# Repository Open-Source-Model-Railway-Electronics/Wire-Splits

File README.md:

# Wire-Splits

TODO:
Make sure they can be made with with SMD assembly

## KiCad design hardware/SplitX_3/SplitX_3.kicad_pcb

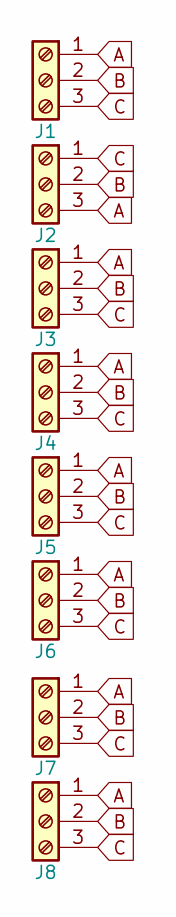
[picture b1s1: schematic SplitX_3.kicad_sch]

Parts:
J1, J2, J3, J4, J5, J6, J7, J8: Screw_Terminal_01x03; TerminalBlock_Phoenix_MKDS-1,5-3-5.08_1x03_P5.08mm_Horizont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

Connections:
A: J1.1, J2.3, J3.1, J4.1, J5.1, J6.1, J7.1, J8.1
B: J1.2, J2.2, J3.2, J4.2, J5.2, J6.2, J7.2, J8.2
C: J1.3, J2.1, J3.3, J4.3, J5.3, J6.3, J7.3, J8.3

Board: 4 copper layers, 8 parts (0 on the bottom side), 3 nets, no tracks yet.

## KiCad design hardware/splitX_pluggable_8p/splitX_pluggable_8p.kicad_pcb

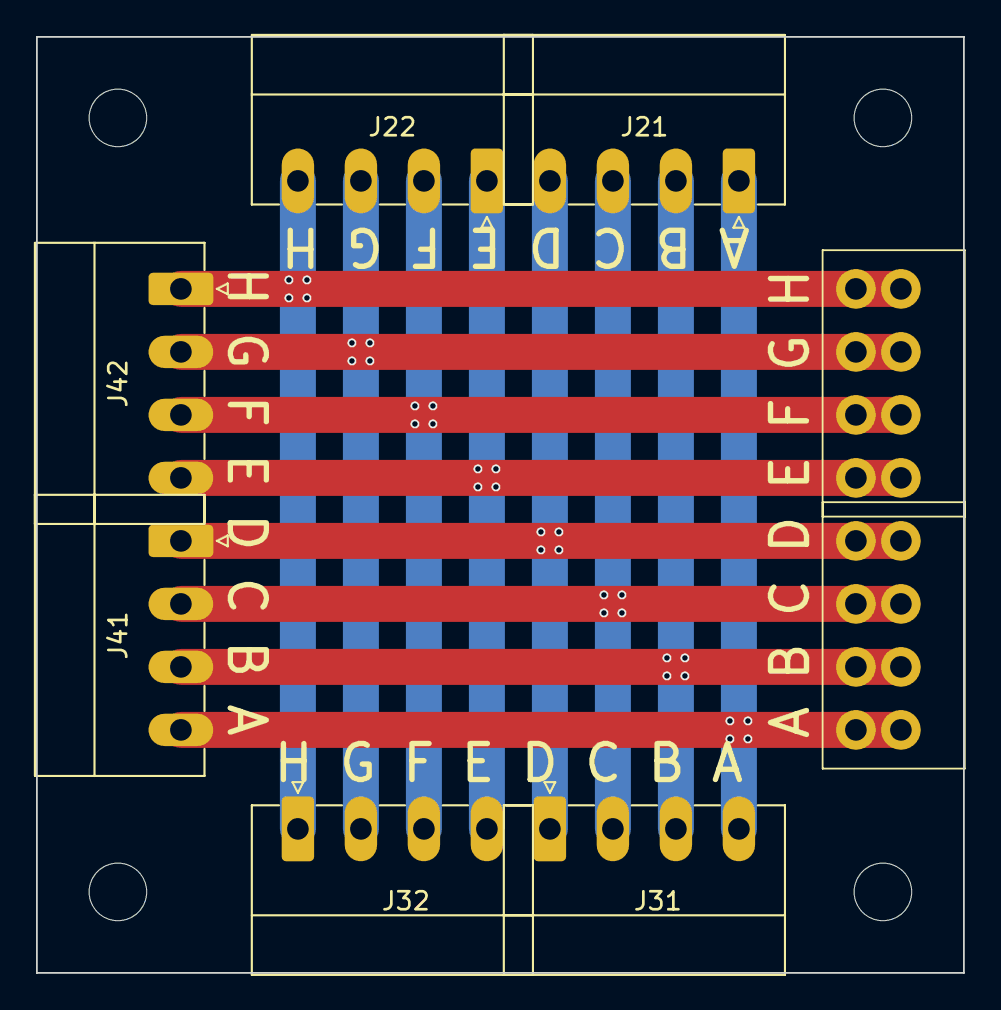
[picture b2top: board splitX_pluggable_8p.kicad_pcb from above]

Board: 2 copper layers, 51.5 x 52.0 mm, 8 parts (0 on the bottom side), 8 nets.

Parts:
J11, J12: MALE; connector_3.50mm_4P horizontal_MALE
J21, J22, J31, J32, J41, J42: FEMALE; PhoenixContact_MC_1,5_4-G-3.5_1x04_P3.50mm_Horizontal

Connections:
unnamed: J11.1, J21.1, J31.4, J41.4
unnamed: J11.2, J21.2, J31.3, J41.3
unnamed: J11.3, J21.3, J31.2, J41.2
unnamed: J11.4, J21.4, J31.1, J41.1
unnamed: J12.1, J22.1, J32.4, J42.4
unnamed: J12.2, J22.2, J32.3, J42.3
unnamed: J12.3, J22.3, J32.2, J42.2
unnamed: J12.4, J22.4, J32.1, J42.1

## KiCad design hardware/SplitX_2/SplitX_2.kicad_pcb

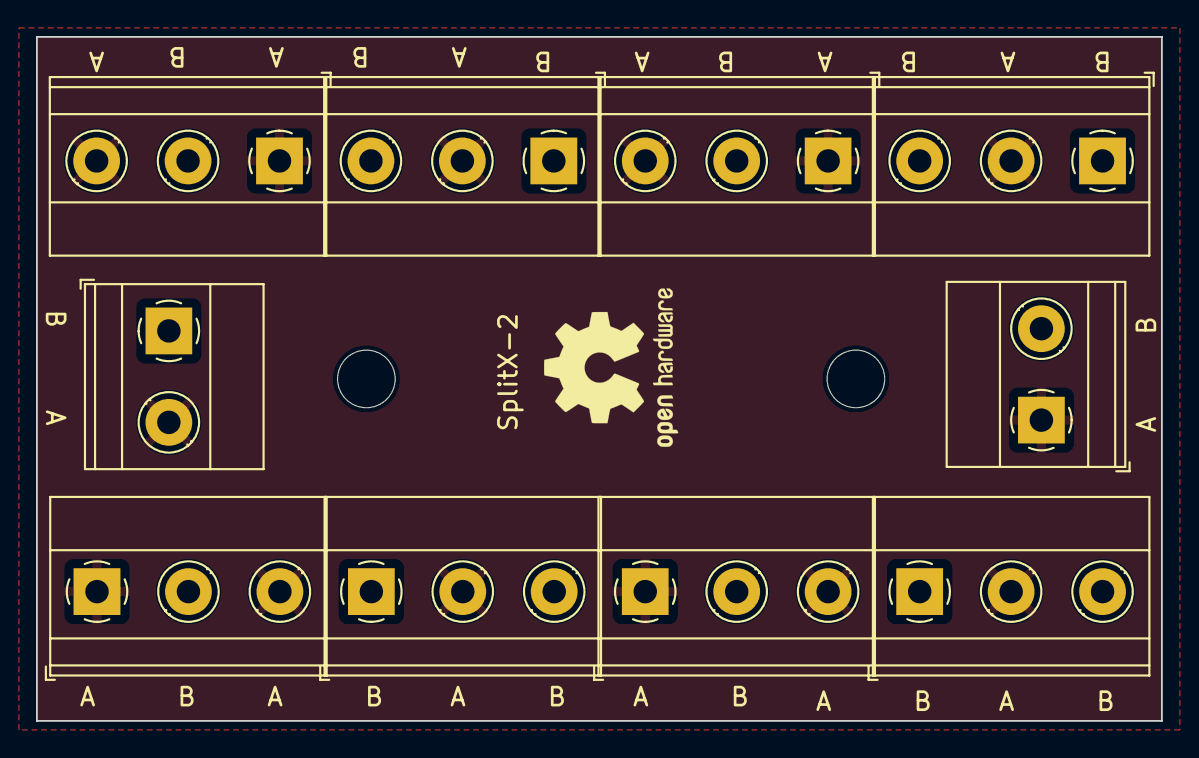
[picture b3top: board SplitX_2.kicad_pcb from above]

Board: 2 copper layers, 62.5 x 38.0 mm, 10 parts (0 on the bottom side), 2 nets, no tracks yet.

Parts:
J1, J10: Screw_Terminal_01x02; TerminalBlock_Phoenix_MKDS-1,5-2-5.08_1x02_P5.08mm_Horizont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
J2, J3, J4, J5, J6, J7, J8, J9: Screw_Terminal_01x03; TerminalBlock_Phoenix_MKDS-1,5-3-5.08_1x03_P5.08mm_Horizont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

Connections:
A: J1.2, J2.2, J3.1, J3.3, J4.1, J4.3, J5.2, J6.2, J7.1, J7.3, J8.1, J8.3, J9.2, J10.1
B: J1.1, J2.1, J2.3, J3.2, J4.2, J5.1, J5.3, J6.1, J6.3, J7.2, J8.2, J9.1, J9.3, J10.2

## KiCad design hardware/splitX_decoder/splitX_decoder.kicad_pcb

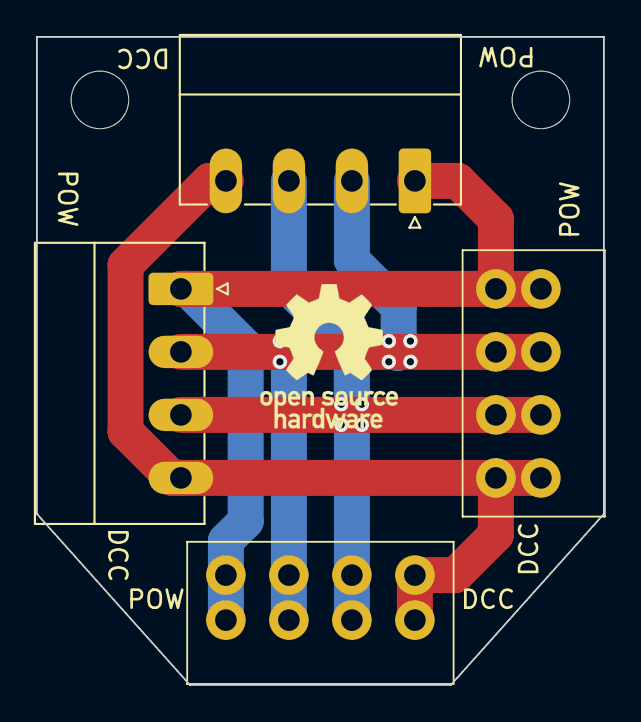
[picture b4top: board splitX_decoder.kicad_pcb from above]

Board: 2 copper layers, 31.5 x 36.0 mm, 4 parts (0 on the bottom side), 4 nets.

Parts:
J101, J102: FEMALE; PhoenixContact_MC_1,5_4-G-3.5_1x04_P3.50mm_Horizontal
J103, J104: MALE; connector_3.50mm_4P horizontal_MALE

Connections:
unnamed: J101.1, J102.1, J103.1, J104.4
unnamed: J101.2, J102.2, J103.2, J104.3
unnamed: J101.3, J102.3, J103.3, J104.2
unnamed: J101.4, J102.4, J103.4, J104.1

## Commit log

2025-06-13 added initial files
2025-06-19 organized this folder and added a picture
2025-06-19 Toegevoegd: handleiding (manual.odt)
2025-06-19 Hersteld: handleiding toegevoegd in docs/
